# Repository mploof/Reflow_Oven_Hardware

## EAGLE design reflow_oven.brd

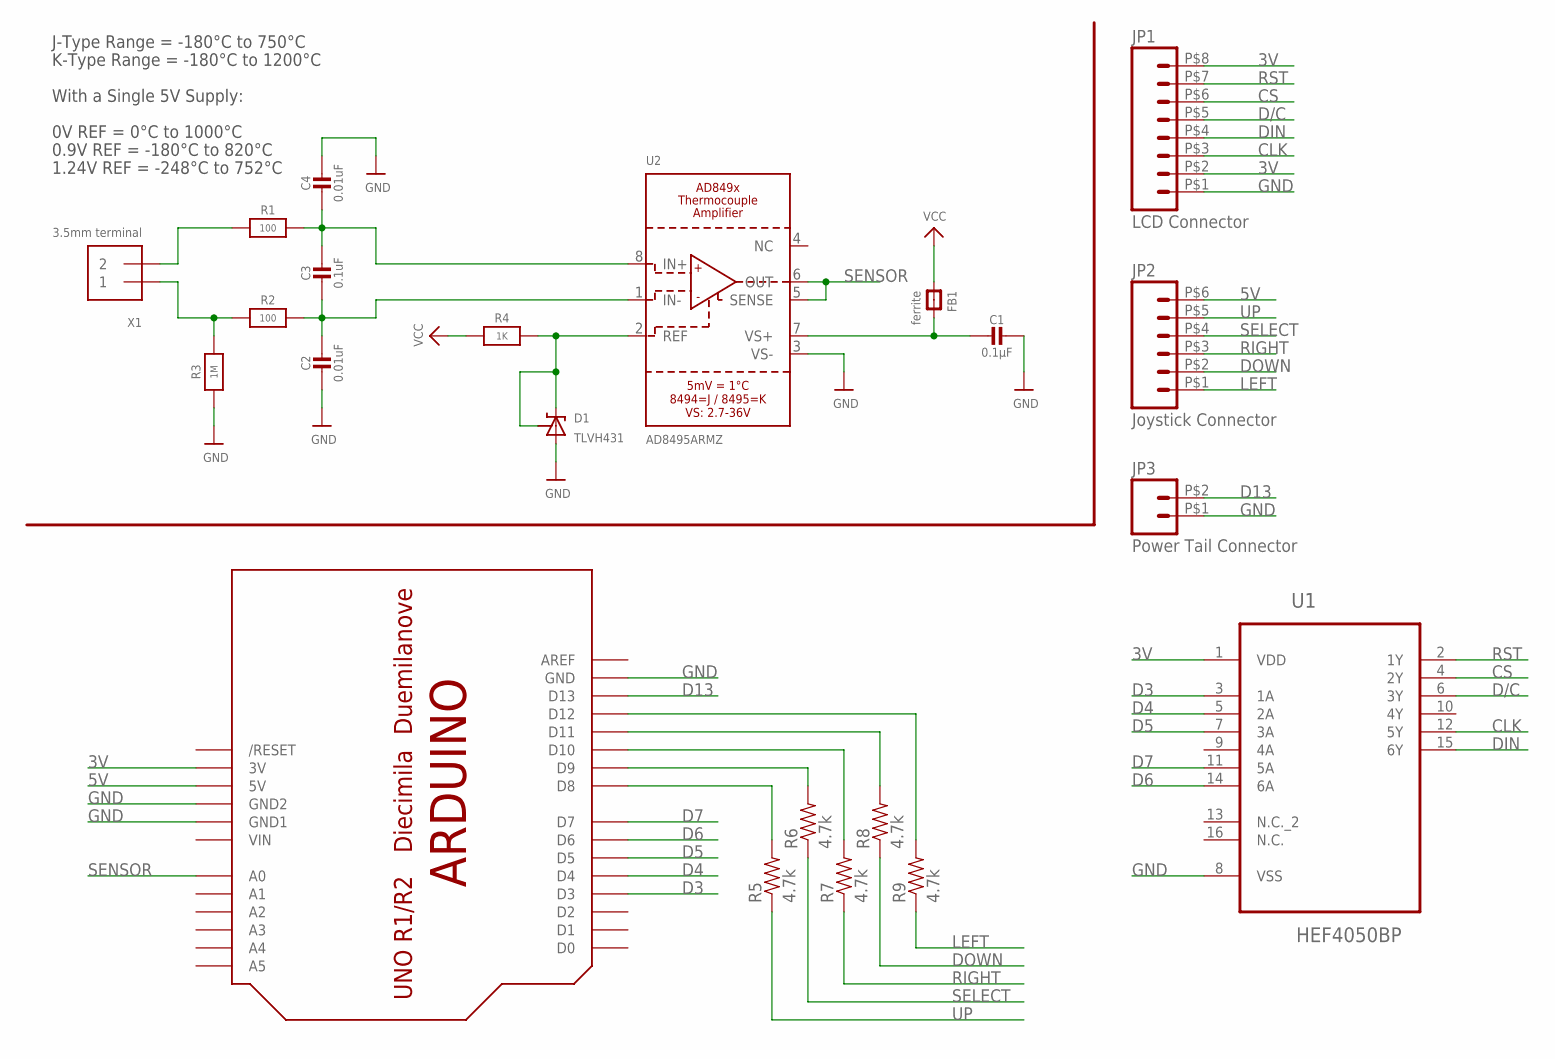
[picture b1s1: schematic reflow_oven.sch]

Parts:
C1: 0.1µF; 0805-NO
C2, C4: 0.01uF; 0805-NO
C3: 0.1uF; 0805-NO
D1: TLVH431; SOT23-R
FB1: ferrite; 0805
JP1: LCD Connector; SPRINGTERMINAL-0.1"-8
JP2: Joystick Connector; SPRINGTERMINAL-0.1"-6
JP3: Power Tail Connector; SPRINGTERMINAL-0.1"-2
R1, R2: 100; 0805-NO
R3: 1M; 0805-NO
R4: 1K; 0805-NO
R5, R6, R7, R8, R9: 4.7k; 0805
U1: HEF4050BP; DIP254P762X420-16
U2: AD8495ARMZ; MSOP8_0.65MM
U$1: ARDUINOUNO; ARDUINO
X1: 3.5mm terminal; TERMBLOCK_1X2-3.5MM

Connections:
3V: JP1.P$2 (2), JP1.P$8 (8), U1.1 (VDD), U$1.3V
5V: JP2.P$6 (6), U$1.5V
CLK: JP1.P$3 (3), U1.12 (5Y)
CS: JP1.P$6 (6), U1.4 (2Y)
D3: U1.3 (1A), U$1.D3
D4: U1.5 (2A), U$1.D4
D5: U1.7 (3A), U$1.D5
D6: U1.14 (6A), U$1.D6
D7: U1.11 (5A), U$1.D7
D8: R5.2, U$1.D8
D13: JP3.P$2 (2), U$1.D13
D/C: JP1.P$5 (5), U1.6 (3Y)
DIN: JP1.P$4 (4), U1.15 (6Y)
DOWN: JP2.P$2 (2), R8.1
GND: C1.1, C2.2, C4.1, D1.3 (A), JP1.P$1 (1), JP3.P$1 (1), R3.1, U1.8 (VSS), U2.3 (VS-), U$1.GND, U$1.GND1, U$1.GND2
IN+: R1.1, X1.2
IN-: R2.1, R3.2, X1.1
LEFT: JP2.P$1 (1), R9.1
unnamed: D1.1 (VREF), D1.2 (C), R4.2, U2.2 (REF)
unnamed: C3.1, C4.2, R1.2, U2.8 (IN+)
unnamed: C2.1, C3.2, R2.2, U2.1 (IN-)
unnamed: C1.2, FB1.2, U2.7 (VS+)
unnamed: R6.2, U$1.D9
unnamed: R7.2, U$1.D10
unnamed: R8.2, U$1.D11
unnamed: R9.2, U$1.D12
RIGHT: JP2.P$3 (3), R7.1
RST: JP1.P$7 (7), U1.2 (1Y)
SELECT: JP2.P$4 (4), R6.1
SENSOR: U2.5 (SENSE), U2.6 (OUT), U$1.A0
UP: JP2.P$5 (5), R5.1
VCC: FB1.1, R4.1
VIN: U$1.VIN

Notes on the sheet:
J-Type Range = -180°C to 750°C
K-Type Range = -180°C to 1200°C
With a Single 5V Supply:
1.24V REF = -248°C to 752°C
0.9V REF = -180°C to 820°C
0V REF = 0°C to 1000°C

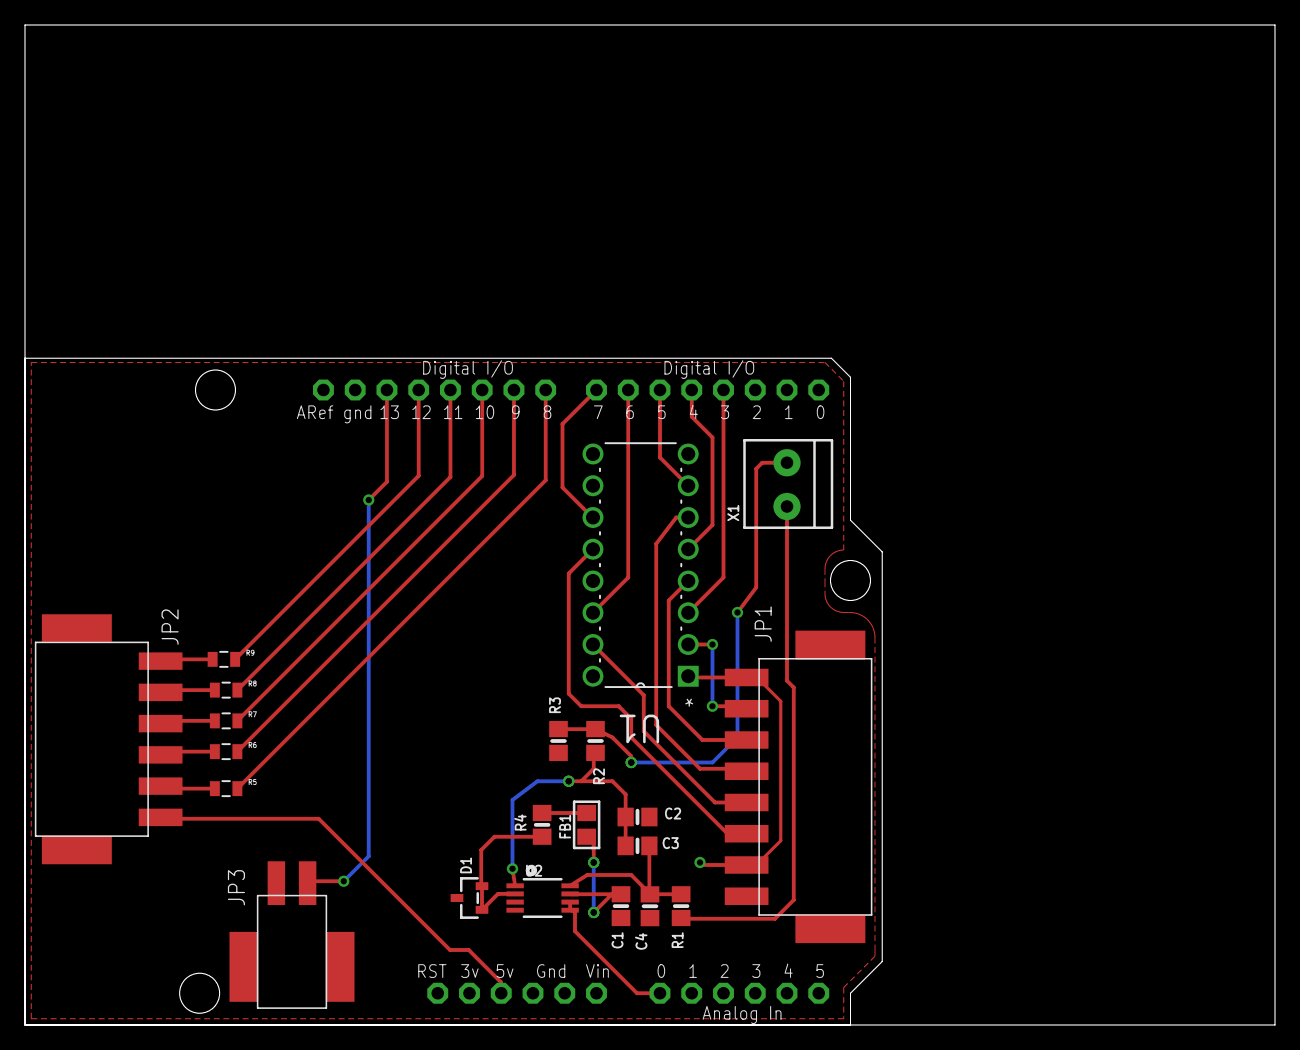
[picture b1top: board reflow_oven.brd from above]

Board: 2 copper layers, 100.0 x 80.0 mm, 22 parts (0 on the bottom side), 32 nets.

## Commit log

2015-08-11 :lollipop: Added .gitattributes & .gitignore files
2015-08-11 Initial commit of reflow oven EagleCAD layout
2015-08-11 Updated .gitignore
2015-08-11 Revert "Updated .gitignore"
    This reverts commit 98f2c45ad1051d1ff4b5d145b1002bec0f862710.

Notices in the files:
parts and their libraries:
SparkFun-Connectors: Licensing: Creative Commons ShareAlike 4.0 International - https://creativecommons.org/licenses/by-sa/4.0
microbuilder: This work is placed in the public domain, and may be freely used for commercial and non-commercial work with the following conditions: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
